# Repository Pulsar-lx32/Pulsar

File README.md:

# lx32

**lx32** is a minimal 32-bit CPU project written in **SystemVerilog**.

> **Purpose**  
> This project's goal is educational: to understand how a CPU works from the ground up, including digital logic, datapaths, control logic, and basic instruction execution.

---

## 🛠️ Quick Start

The LX32 environment is **fully automated**. To compile the RTL-to-Rust bridge, build the validator, and run the full test suite:

```bash
make setup
```

> **Note:**  
> Requires `verilator` and the Rust toolchain installed.

---

## 🎯 Goals

- Learn computer architecture by building it.
- Practice SystemVerilog through real hardware design.
- Keep the design simple, readable, and well-documented.

---

## 🚫 Non-Goals

- High performance.
- Feature completeness.
- Production-ready silicon.

---

## 🏗️ Project Scope

- Custom 32-bit architecture.
- Simple instruction set.
- Incremental development and testing.
- Simulation-first approach.

---

## ✅ Verification and Robustness

The LX32 architecture undergoes comprehensive stress testing via a custom **Rust-based validator**.

| Module         | Iterations     | Status  |
| -------------- | ------------- | ------- |
| ALU Core       | 100,000,000   | PASSED  |
| Branch Unit    | 100,000,000   | PASSED  |
| Control Unit   | 100,000,000   | PASSED  |
| Register File  | 100,000,000   | PASSED  |
| Full System    | 100,000,000   | PASSED  |

**Total random vectors processed:**  
_Approximately 1.1 Billion in under 75 seconds._

---

## 📄 License

MIT

---

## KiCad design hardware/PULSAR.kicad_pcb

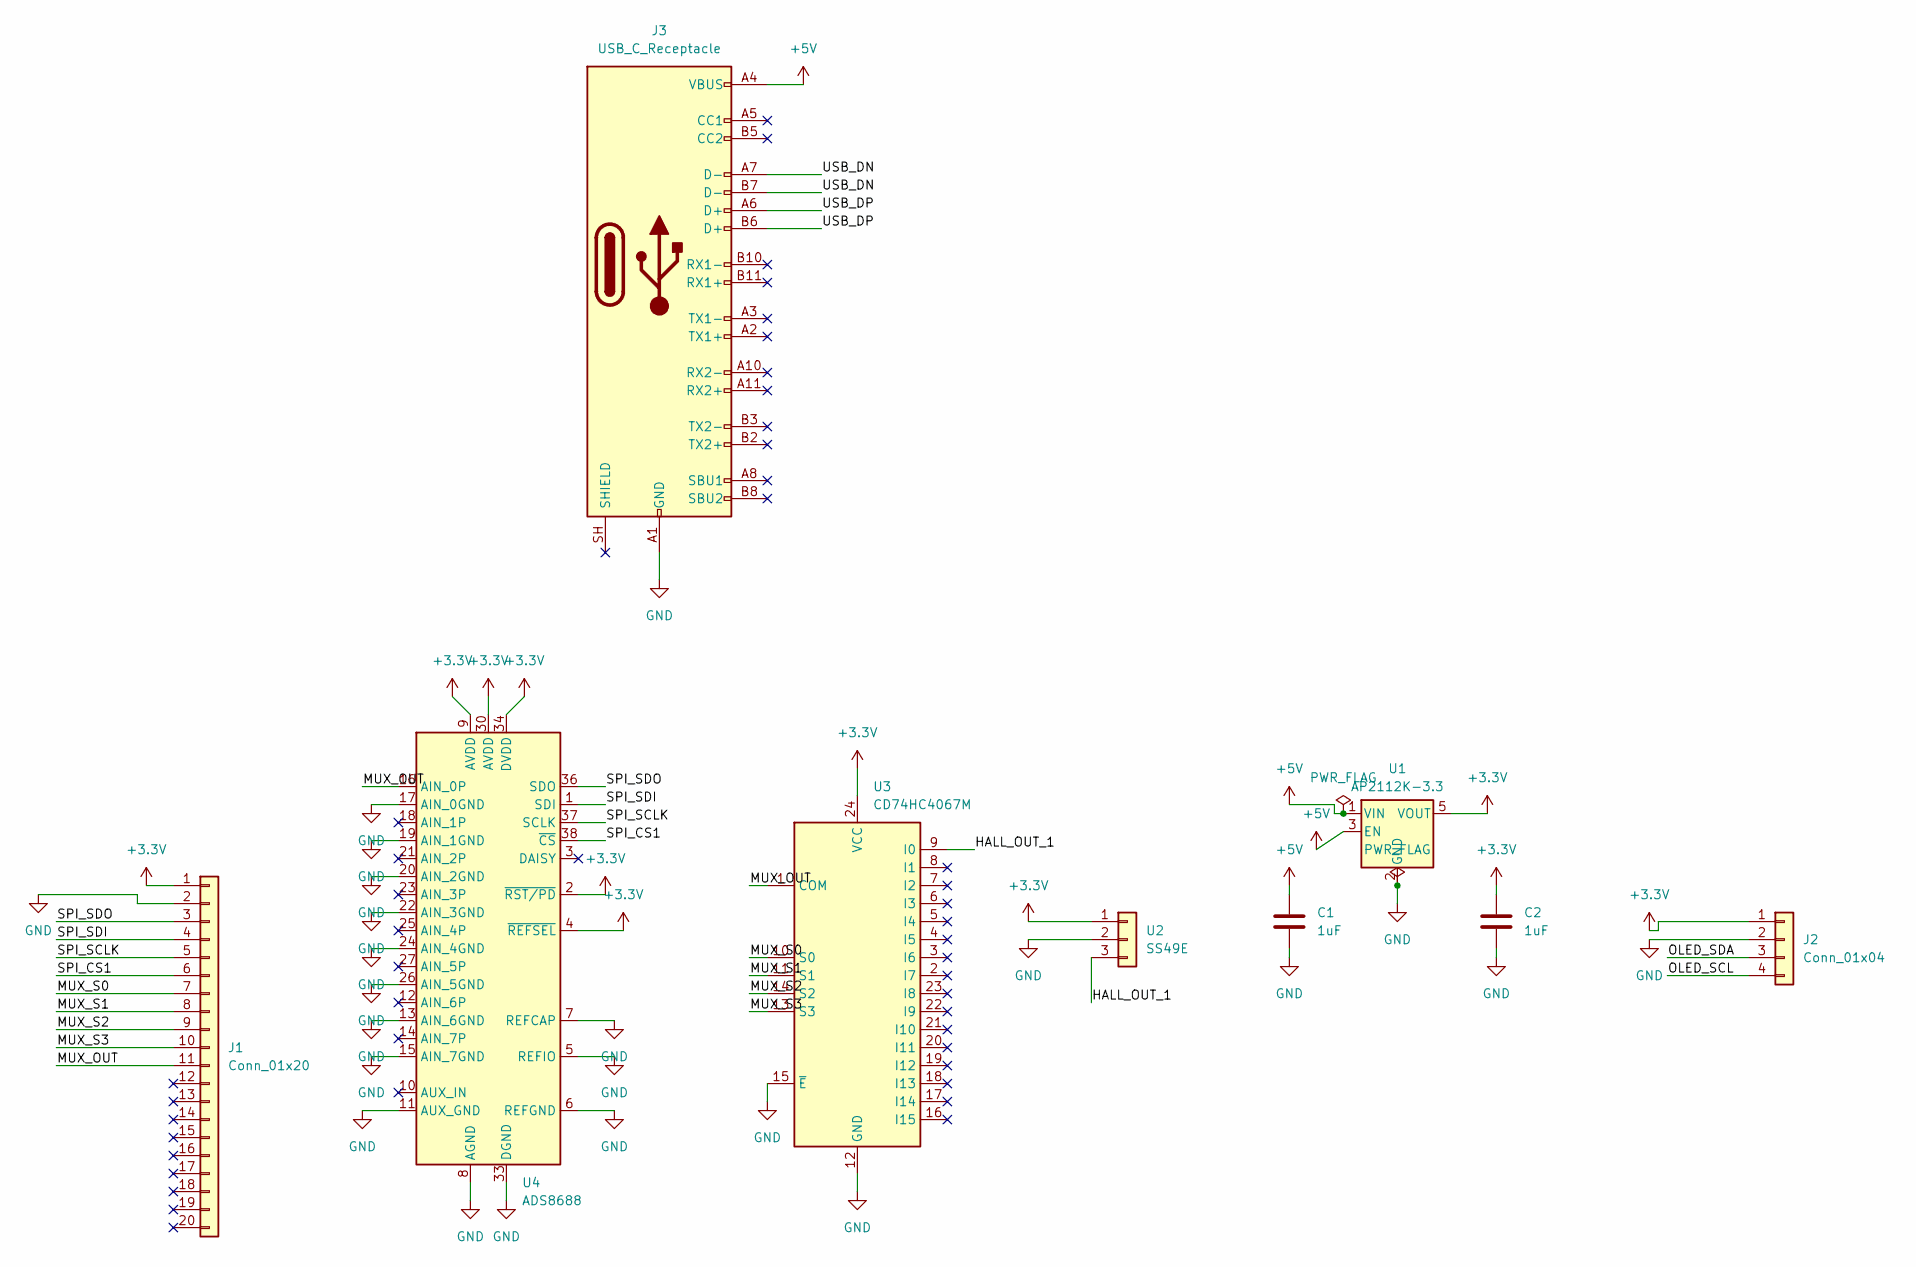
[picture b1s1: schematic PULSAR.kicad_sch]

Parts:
C1, C2: 1uF
J1: Conn_01x20
J2: Conn_01x04
J3: USB_C_Receptacle
U1: AP2112K-3.3; SOT-23-5
U2: SS49E
U3: CD74HC4067M; SOIC-24W_7.5x15.4mm_P1.27mm
U4: ADS8688; TSSOP-38_4.4x9.7mm_P0.5mm

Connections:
+3.3V: C2.1, J1.1, J2.1, U1.5 (VOUT), U2.1, U3.24 (VCC), U4.2 (~RST/PD), U4.4 (~REFSEL), U4.9 (AVDD), U4.30 (AVDD), U4.34 (DVDD)
+5V: C1.1, J3.A4 (VBUS), J3.A9 (VBUS), J3.B4 (VBUS), J3.B9 (VBUS), U1.1 (VIN), U1.3 (EN)
/HALL_OUT_1: U2.3, U3.9 (I0)
/MUX_OUT: J1.11, U3.1 (COM), U4.16 (AIN_0P)
/MUX_S0: J1.7, U3.10 (S0)
/MUX_S1: J1.8, U3.11 (S1)
/MUX_S2: J1.9, U3.14 (S2)
/MUX_S3: J1.10, U3.13 (S3)
/OLED_SCL: J2.4
/OLED_SDA: J2.3
/SPI_CS1: J1.6, U4.38 (~CS)
/SPI_SCLK: J1.5, U4.37 (SCLK)
/SPI_SDI: J1.4, U4.1 (SDI)
/SPI_SDO: J1.3, U4.36 (SDO)
/USB_DN: J3.A7 (D-), J3.B7 (D-)
/USB_DP: J3.A6 (D+), J3.B6 (D+)
GND: C1.2, C2.2, J1.2, J2.2, J3.A1 (GND), J3.A12 (GND), J3.B1 (GND), J3.B12 (GND), U1.2 (GND), U2.2, U3.12 (GND), U3.15 (~E), U4.5 (REFIO), U4.6 (REFGND), U4.7 (REFCAP), U4.8 (AGND), U4.11 (AUX_GND), U4.13 (AIN_6GND), U4.15 (AIN_7GND), U4.17 (AIN_0GND), U4.19 (AIN_1GND), U4.20 (AIN_2GND), U4.22 (AIN_3GND), U4.24 (AIN_4GND), U4.26 (AIN_5GND), U4.28 (AGND), U4.29 (AGND), U4.31 (AGND), U4.32 (AGND), U4.33 (DGND)

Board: 4 copper layers, 9 parts (0 on the bottom side), 15 nets, no tracks yet.

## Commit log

2026-03-08 Tests/seed tests (#50)
    * Add .gitignore to exclude IDE and local configuration files
    * feat: Add advanced_validation.md documenting reproducible seeds, long program generation, and automatic shrinking for validator
    * docs: Add architecture.md documenting LX32 validator technical implementation and module structure
    * chore: update Cargo.lock to add clap and related dependencies
    * chore: add clap dependency with derive feature to Cargo.toml
    * feat: add cli.rs implementing command-line argument parsing and validation config for LX32 validator
2026-03-08 Refactor Rust CI workflow and update dependencies (#55)
2026-03-08 Feat/setup executable dx (#56)
    * feat: implement 'make setup' and modernize README architecture
    * ci: migrate rust workflow to use 'make setup'
2026-03-08 chore: remove duplicated :help in Makefile (#57)
2026-03-08 Add CODEOWNERS file for repository ownership (#60)
2026-03-08 Docs/refactor documentation (#67)
    * Update .gitignore to exclude .idea directory
    * docs: alu.md documenting golden model ALU design, API, and validation
    * docs: add alu.md documenting RTL ALU design, interface, and integration
    * docs: add alu.md documenting RTL ALU design, interface, and integration
    * docs: add branch_unit.md documenting golden model branch unit design, interface, and validation
    * docs: add branch_unit.md documenting RTL branch unit design, interface, and integration
2026-04-01 feat(tablegen): fix pointer regclass mapping and pseudo overrides (#72)
    - Added RemapAllTargetPseudoPointerOperands to fix ptr_rc errors.
    - Fixed instruction property inference (mayLoad/mayStore).
    - Organized includes and fixed Pseudo class scope.
    - Added compile_td.sh utility script.
2026-04-01 Remove LX32 instruction definitions (#74)
2026-04-02 Feat/llvm backend llc (#77)
    * feat: added Subtarget in the script to generate an .inc file
    * feat: add minimal Subtarget and TargetMachine stubs
    - Register Subtarget/TargetMachine sources in LX32CodeGen CMake target
    - Provide minimal buildable LX32Subtarget and LX32TargetMachine skeletons
    - Add placeholder headers for lowering/frame/reg/instr info (stubs)
    * feat: reorganize CMakeLists to streamline target structure
2026-04-07 fix: fixed the issue with ctr0.S and link.ld (#84)
2026-04-08 backend: harden baremetal flow, add deep tests and optimized-C docs (#86)
2026-04-09 Add license section with MIT license
2026-04-09 Add license section with MIT license (#1)
2026-04-10 chore: change the clone command with the custom llvm fork
2026-04-10 feat: add power section schematic AP2112K-3.3 LDO 5V to 3.3V
2026-04-10 feat: add Hall sensor SS49E schematic with HALL_OUT_1 net
2026-04-10 feat: add OLED SSD1306 connector with SPI signals
2026-04-10 feat: add USB-C connector with power and data signals
2026-04-11 fix: resolve ERC errors, add PWR_FLAG and DAISY no-connect
2026-04-11 feat: setup 4-layer PCB and import schematic footprints
2026-04-11 build: add docker build context files required by CI workflow
2026-04-11 ci: trigger backend toolchain workflow on sandbox branches
2026-04-11 ci: speed up backend pipeline with nproc, path filters, and branch-gated image push
2026-04-12 feat: complete PCB routing and fix DRC errors
2026-04-12 feat: generate gerber files for JLCPCB manufacturing
2026-04-12 backend: fix BR_CC pseudo lowering crash in branch loop
2026-04-12 lx32: harden BRCC lowering and gate toolchain artifacts on backend tests
2026-04-12 lx32/isel: revert branch SelectNodeTo experiment
2026-04-12 lx32/isel: normalize BRCC constants in lowering
2026-04-12 backend: stabilize BRCC lowering/isel path and fix branch-loop crash
2026-04-12 Fix operand order for CALL in ISel
2026-04-12 Fix call selection regression and PseudoRET live-outs
2026-04-12 Select BR via TableGen pattern for PseudoBR
2026-04-12 Custom-lower BRCOND to BRCC for i1 branch conditions
2026-04-12 Use backend hash cache-bust instead of no-cache
2026-04-12 Fix PseudoCALL operand order in DAG isel
2026-04-13 fix(lx32): stabilize deep baremetal path and local build flow
2026-04-13 docs: added initial documentation of technical backend decisions
2026-04-14 feat: full integration of LX custom ISA and hardware controllers
2026-04-16 feat: esquemático base completo - USB-C, OLED SPI, OrangeCrab, ADS8688
2026-04-16 feat: update gitignore and add benchmark summary tools
2026-04-16 feat: add intrinsics for lx32k custom isa and rust target spec
2026-04-16 docs: add pulsar-pac and comprehensive firmware development guide
2026-04-17 feat: complete BOM with verified LCSC part numbers
2026-04-22 Remove @AgusVegaa from CODEOWNERS
2026-04-22 Remove @AgusVegaa from CODEOWNERS (#12)
2026-04-26 Kicad (#11)
    * feat: esquemático base completo - USB-C, OLED SPI, OrangeCrab, ADS8688
    * feat: complete BOM with verified LCSC part numbers
    * feat: PCB routing in progress - power and SPI connections
    ---------
